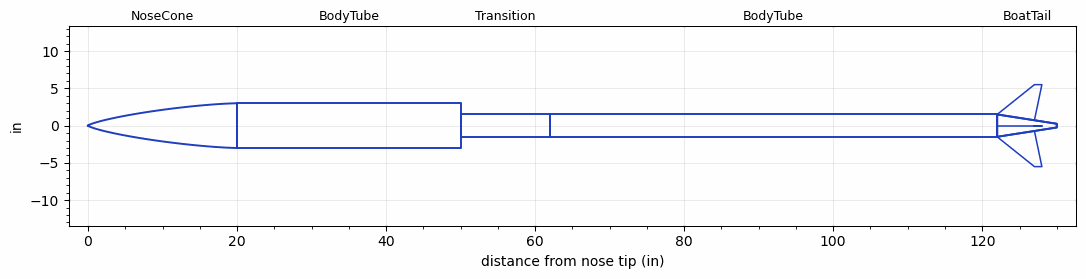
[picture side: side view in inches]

<RASAeroDocument>
 <FileVersion>2</FileVersion>
 <RocketDesign>
  <NoseCone>
   <Length>20</Length>
   <Diameter>6</Diameter>
   <Shape>Von Karman Ogive</Shape>
   <BluntRadius>0.1</BluntRadius>
   <Location>0</Location>
  </NoseCone>
  <BodyTube>
   <Length>30</Length>
   <Diameter>6</Diameter>
   <Location>20</Location>
  </BodyTube>
  <Transition>
   <Length>12</Length>
   <Diameter>3</Diameter>
   <Location>50</Location>
   <RearDiameter>3</RearDiameter>
  </Transition>
  <BodyTube>
   <Length>60</Length>
   <Diameter>3</Diameter>
   <Location>62</Location>
   <BoattailLength>8</BoattailLength>
   <BoattailRearDiameter>0.5</BoattailRearDiameter>
  </BodyTube>
  <BoatTail>
   <Length>8</Length>
   <Diameter>3</Diameter>
   <RearDiameter>0.5</RearDiameter>
   <Location>122</Location>
   <Fin>
    <Count>4</Count>
    <Chord>5</Chord>
    <Span>4</Span>
    <SweepDistance>5</SweepDistance>
    <TipChord>1</TipChord>
    <Thickness>0.12</Thickness>
    <LERadius>0.01</LERadius>
    <Location>8</Location>
    <AirfoilSection>Double Wedge</AirfoilSection>
    <FX1>0.45</FX1>
   </Fin>
  </BoatTail>
  <Surface>Smooth Paint</Surface>
  <ModifiedBarrowman>True</ModifiedBarrowman>
  <Turbulence>True</Turbulence>
  <UseBooster1>False</UseBooster1>
  <UseBooster2>False</UseBooster2>
 </RocketDesign>
 <LaunchSite>
  <Altitude>800</Altitude>
  <Pressure>0</Pressure>
  <RodAngle>0</RodAngle>
  <RodLength>12</RodLength>
  <Temperature>85</Temperature>
  <WindSpeed>0</WindSpeed>
 </LaunchSite>
 <Recovery>
  <Altitude1>1000</Altitude1>
  <Altitude2>1000</Altitude2>
  <DeviceType1>Parachute</DeviceType1>
  <DeviceType2>None</DeviceType2>
  <Event1>False</Event1>
  <Event2>False</Event2>
  <Size1>0</Size1>
  <Size2>1</Size2>
  <EventType1>Apogee</EventType1>
  <EventType2>None</EventType2>
  <CD1>0</CD1>
  <CD2>1.33</CD2>
 </Recovery>
 <SimulationList>
  <Simulation>
   <SustainerEngine>O6000W  (AeroTech)</SustainerEngine>
   <SustainerLaunchWt>180</SustainerLaunchWt>
   <SustainerNozzleDiameter>4</SustainerNozzleDiameter>
   <SustainerCG>55</SustainerCG>
   <SustainerIgnitionDelay>0</SustainerIgnitionDelay>
   <Booster1SeparationDelay>0</Booster1SeparationDelay>
   <Booster1IgnitionDelay>0</Booster1IgnitionDelay>
   <IncludeBooster1>False</IncludeBooster1>
   <Booster2Delay>0</Booster2Delay>
   <IncludeBooster2>False</IncludeBooster2>
   <TimetoApogee>55.60667</TimetoApogee>
   <MaxAltitude>45390.57</MaxAltitude>
   <MaxVelocity>1764.08</MaxVelocity>
  </Simulation>
  <Simulation>
   <SustainerEngine>R100000000  (C-Dog)</SustainerEngine>
   <SustainerLaunchWt>200</SustainerLaunchWt>
   <SustainerNozzleDiameter>4</SustainerNozzleDiameter>
   <SustainerCG>30</SustainerCG>
   <SustainerIgnitionDelay>0</SustainerIgnitionDelay>
   <Booster1SeparationDelay>0</Booster1SeparationDelay>
   <Booster1IgnitionDelay>0</Booster1IgnitionDelay>
   <IncludeBooster1>False</IncludeBooster1>
   <Booster2Delay>0</Booster2Delay>
   <IncludeBooster2>False</IncludeBooster2>
   <TimetoApogee>91.93123</TimetoApogee>
   <MaxAltitude>128237.3</MaxAltitude>
   <MaxVelocity>2956.119</MaxVelocity>
  </Simulation>
 </SimulationList>
</RASAeroDocument>
